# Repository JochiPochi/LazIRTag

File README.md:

# LaZIR Tag
Arduino based LaserTag System

BOM: https://docs.google.com/a/cyphyworks.com/spreadsheets/d/1MXdYDq4qyfqy3L1gnKtGEeZ4zqiRnnMYT2sN9ClZJ-U/edit?usp=sharing

REFERENCE:

IR Receiver Info - http://uk.farnell.com/vishay/tsop4838/ir-receiver-38khz/dp/4913190

IR Receiver Datasheet - http://www.farnell.com/datasheets/1693301.pdf

IR Reference - https://learn.adafruit.com/downloads/pdf/ir-sensor.pdf

Wifi Reference - https://espressif.com/en/products/esp8266/

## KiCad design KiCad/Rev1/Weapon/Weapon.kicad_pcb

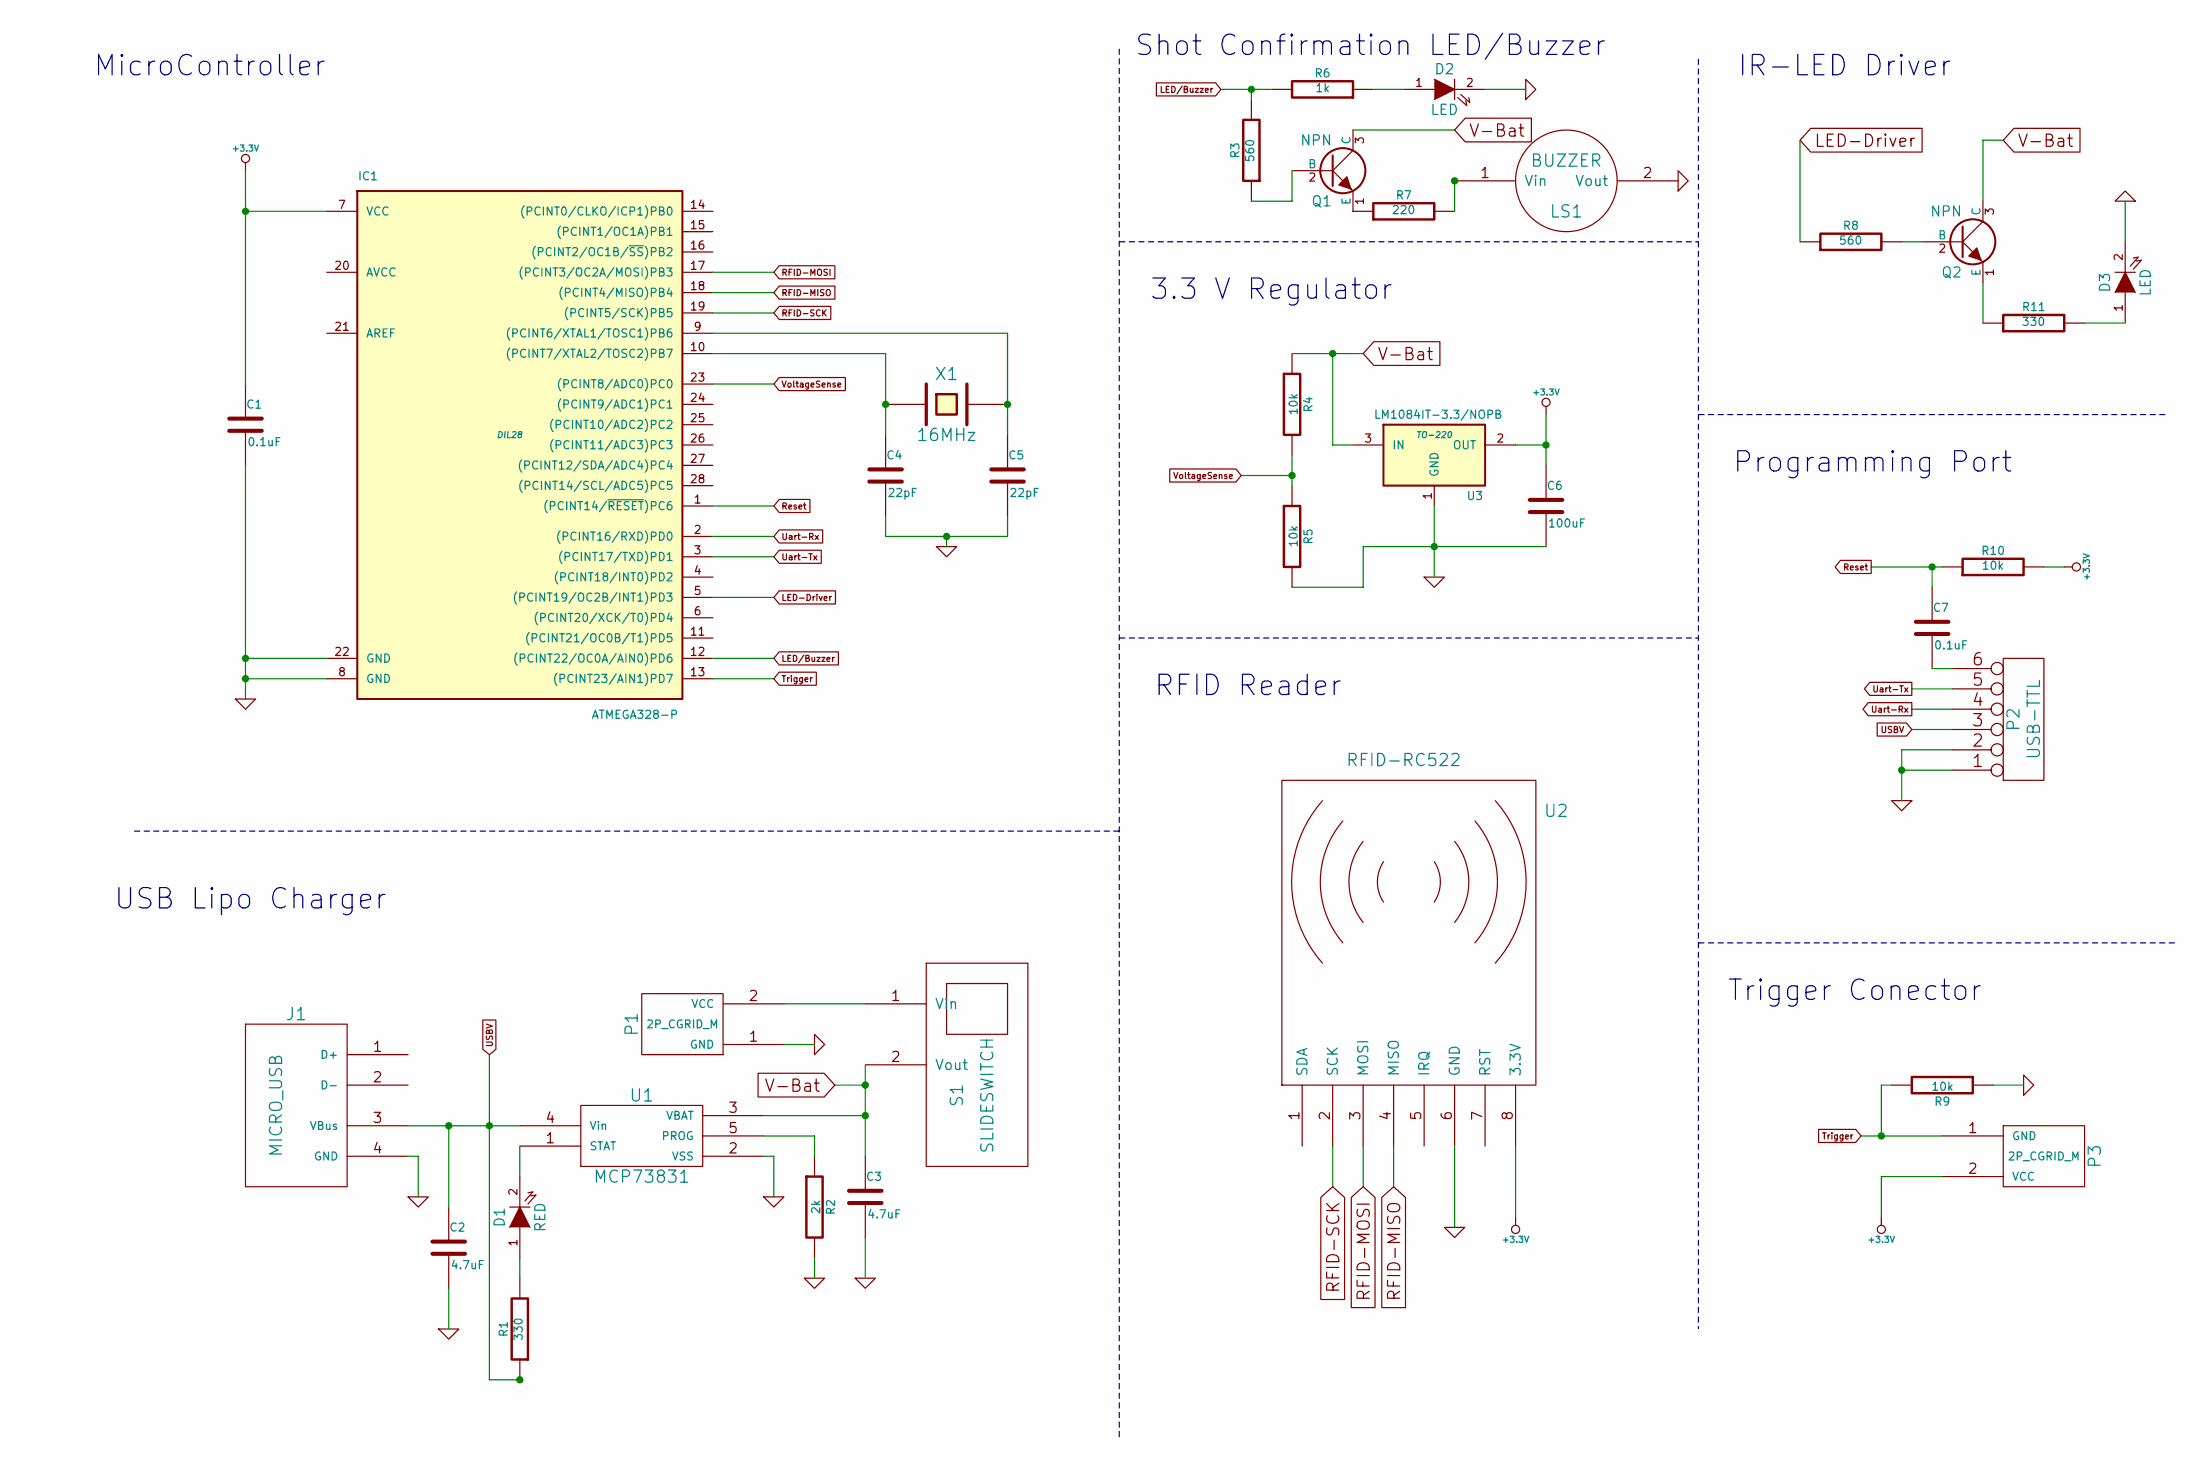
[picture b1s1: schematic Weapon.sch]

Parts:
C1, C7: 0.1uF
C2, C3: 4.7uF
C4, C5: 22pF
C6: 100uF
D1: RED
D2, D3: LED
IC1: ATMEGA328-P; DIL28
J1: MICRO_USB
LS1: BUZZER
P1: 2P_CGRID_M
P2: USB-TTL
P3: 2P_CGRID_M
Q1, Q2: NPN
R1, R11: 330
R2: 2k
R3, R8: 560
R4, R5, R9, R10: 10k
R6: 1k
R7: 220
S1: SLIDESWITCH
U1: MCP73831
U2: RFID-RC522
U3: LM1084IT-3.3/NOPB; TO-220
X1: 16MHz

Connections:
+3.3V: C1.1, C6.1, IC1.7 (VCC), P3.2 (VCC), R10.2, U2.8 (3.3V), U3.2 (OUT)
GND: C1.2, C2.2, C3.2, C4.2, C5.2, C6.2, D2.2 (K), D3.2 (K), IC1.8 (GND), IC1.22 (GND), J1.4 (GND), LS1.2 (Vout), P1.1 (GND), P2.1, P2.2, R2.2, R5.2, R9.1, U1.2 (VSS), U2.6 (GND), U3.1 (GND)
LED-Driver: IC1.5 ((PCINT19/OC2B/INT1)PD3), R8.1
LED/Buzzer: IC1.12 ((PCINT22/OC0A/AIN0)PD6), R3.2, R6.2
unnamed: P1.2 (VCC), S1.1 (Vin)
unnamed: D1.2 (K), U1.1 (STAT)
unnamed: D1.1 (A), R1.2
unnamed: R2.1, U1.5 (PROG)
unnamed: Q1.2 (B), R3.1
unnamed: Q1.1 (E), R7.1
unnamed: LS1.1 (Vin), R7.2
unnamed: D2.1 (A), R6.1
unnamed: C5.1, IC1.9 ((PCINT6/XTAL1/TOSC1)PB6), X1.2
unnamed: C4.1, IC1.10 ((PCINT7/XTAL2/TOSC2)PB7), X1.1
unnamed: C7.2, P2.6
unnamed: Q2.2 (B), R8.2
unnamed: D3.1 (A), R11.2
unnamed: Q2.1 (E), R11.1
RFID-MISO: IC1.18 ((PCINT4/MISO)PB4), U2.4 (MISO)
RFID-MOSI: IC1.17 ((PCINT3/OC2A/MOSI)PB3), U2.3 (MOSI)
RFID-SCK: IC1.19 ((PCINT5/SCK)PB5), U2.2 (SCK)
Reset: C7.1, IC1.1 ((PCINT14/~RESET~)PC6), R10.1
Trigger: IC1.13 ((PCINT23/AIN1)PD7), P3.1 (GND), R9.2
USBV: C2.1, J1.3 (VBus), P2.3, R1.1, U1.4 (Vin)
Uart-Rx: IC1.2 ((PCINT16/RXD)PD0), P2.4
Uart-Tx: IC1.3 ((PCINT17/TXD)PD1), P2.5
V-Bat: C3.1, Q1.3 (C), Q2.3 (C), R4.1, S1.2 (Vout), U1.3 (VBAT), U3.3 (IN)
VoltageSense: IC1.23 ((PCINT8/ADC0)PC0), R4.2, R5.1

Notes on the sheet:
MicroController
Shot Confirmation LED/Buzzer
3.3 V Regulator
RFID Reader
USB Lipo Charger
IR-LED Driver
Programming Port
Trigger Conector

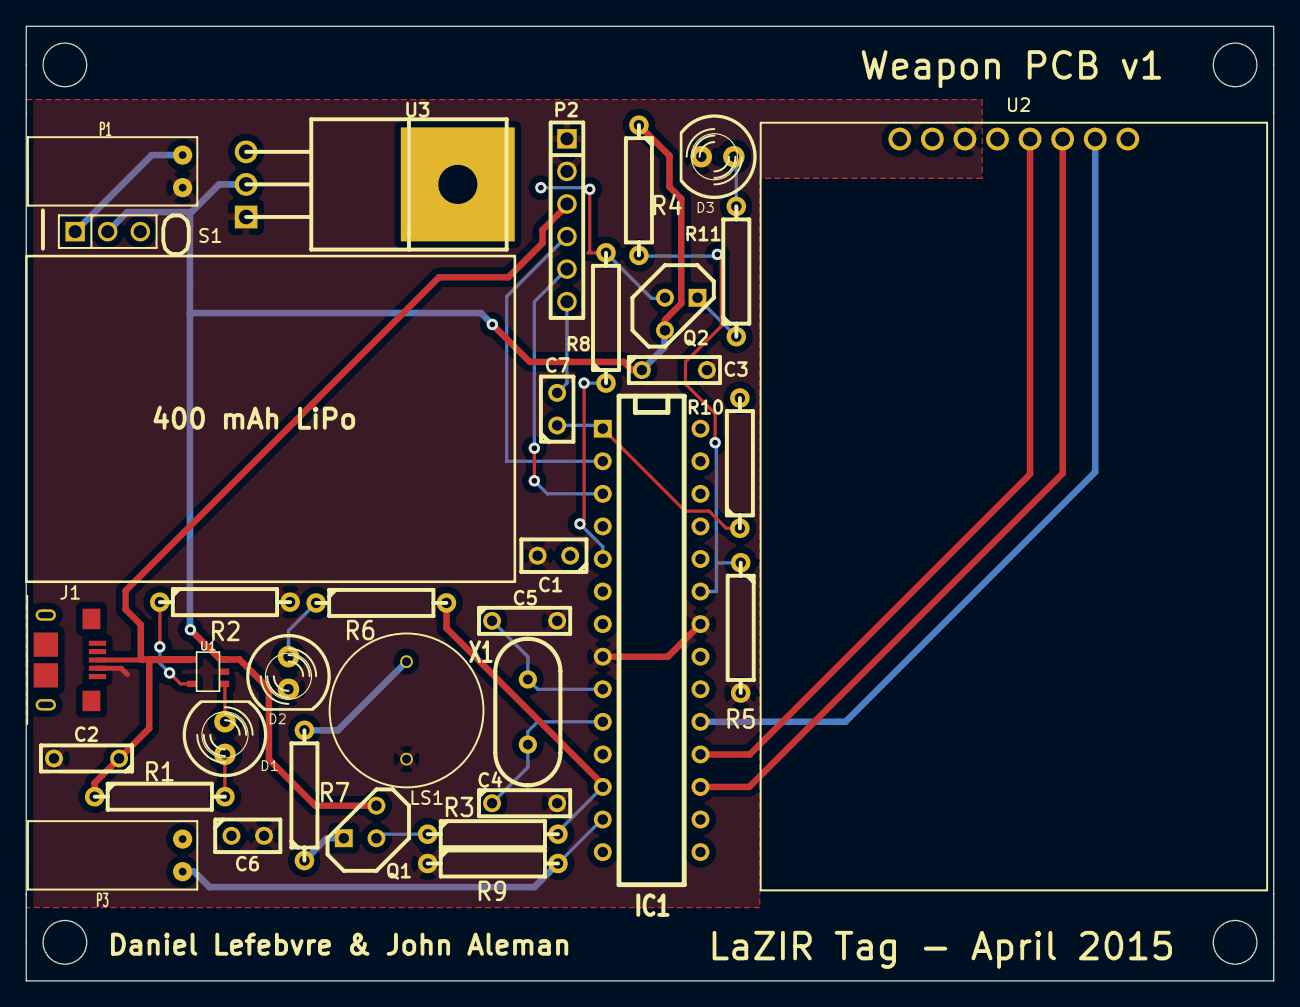
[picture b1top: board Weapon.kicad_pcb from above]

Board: 2 copper layers, 97.3 x 74.4 mm, 34 parts (0 on the bottom side), 28 nets.

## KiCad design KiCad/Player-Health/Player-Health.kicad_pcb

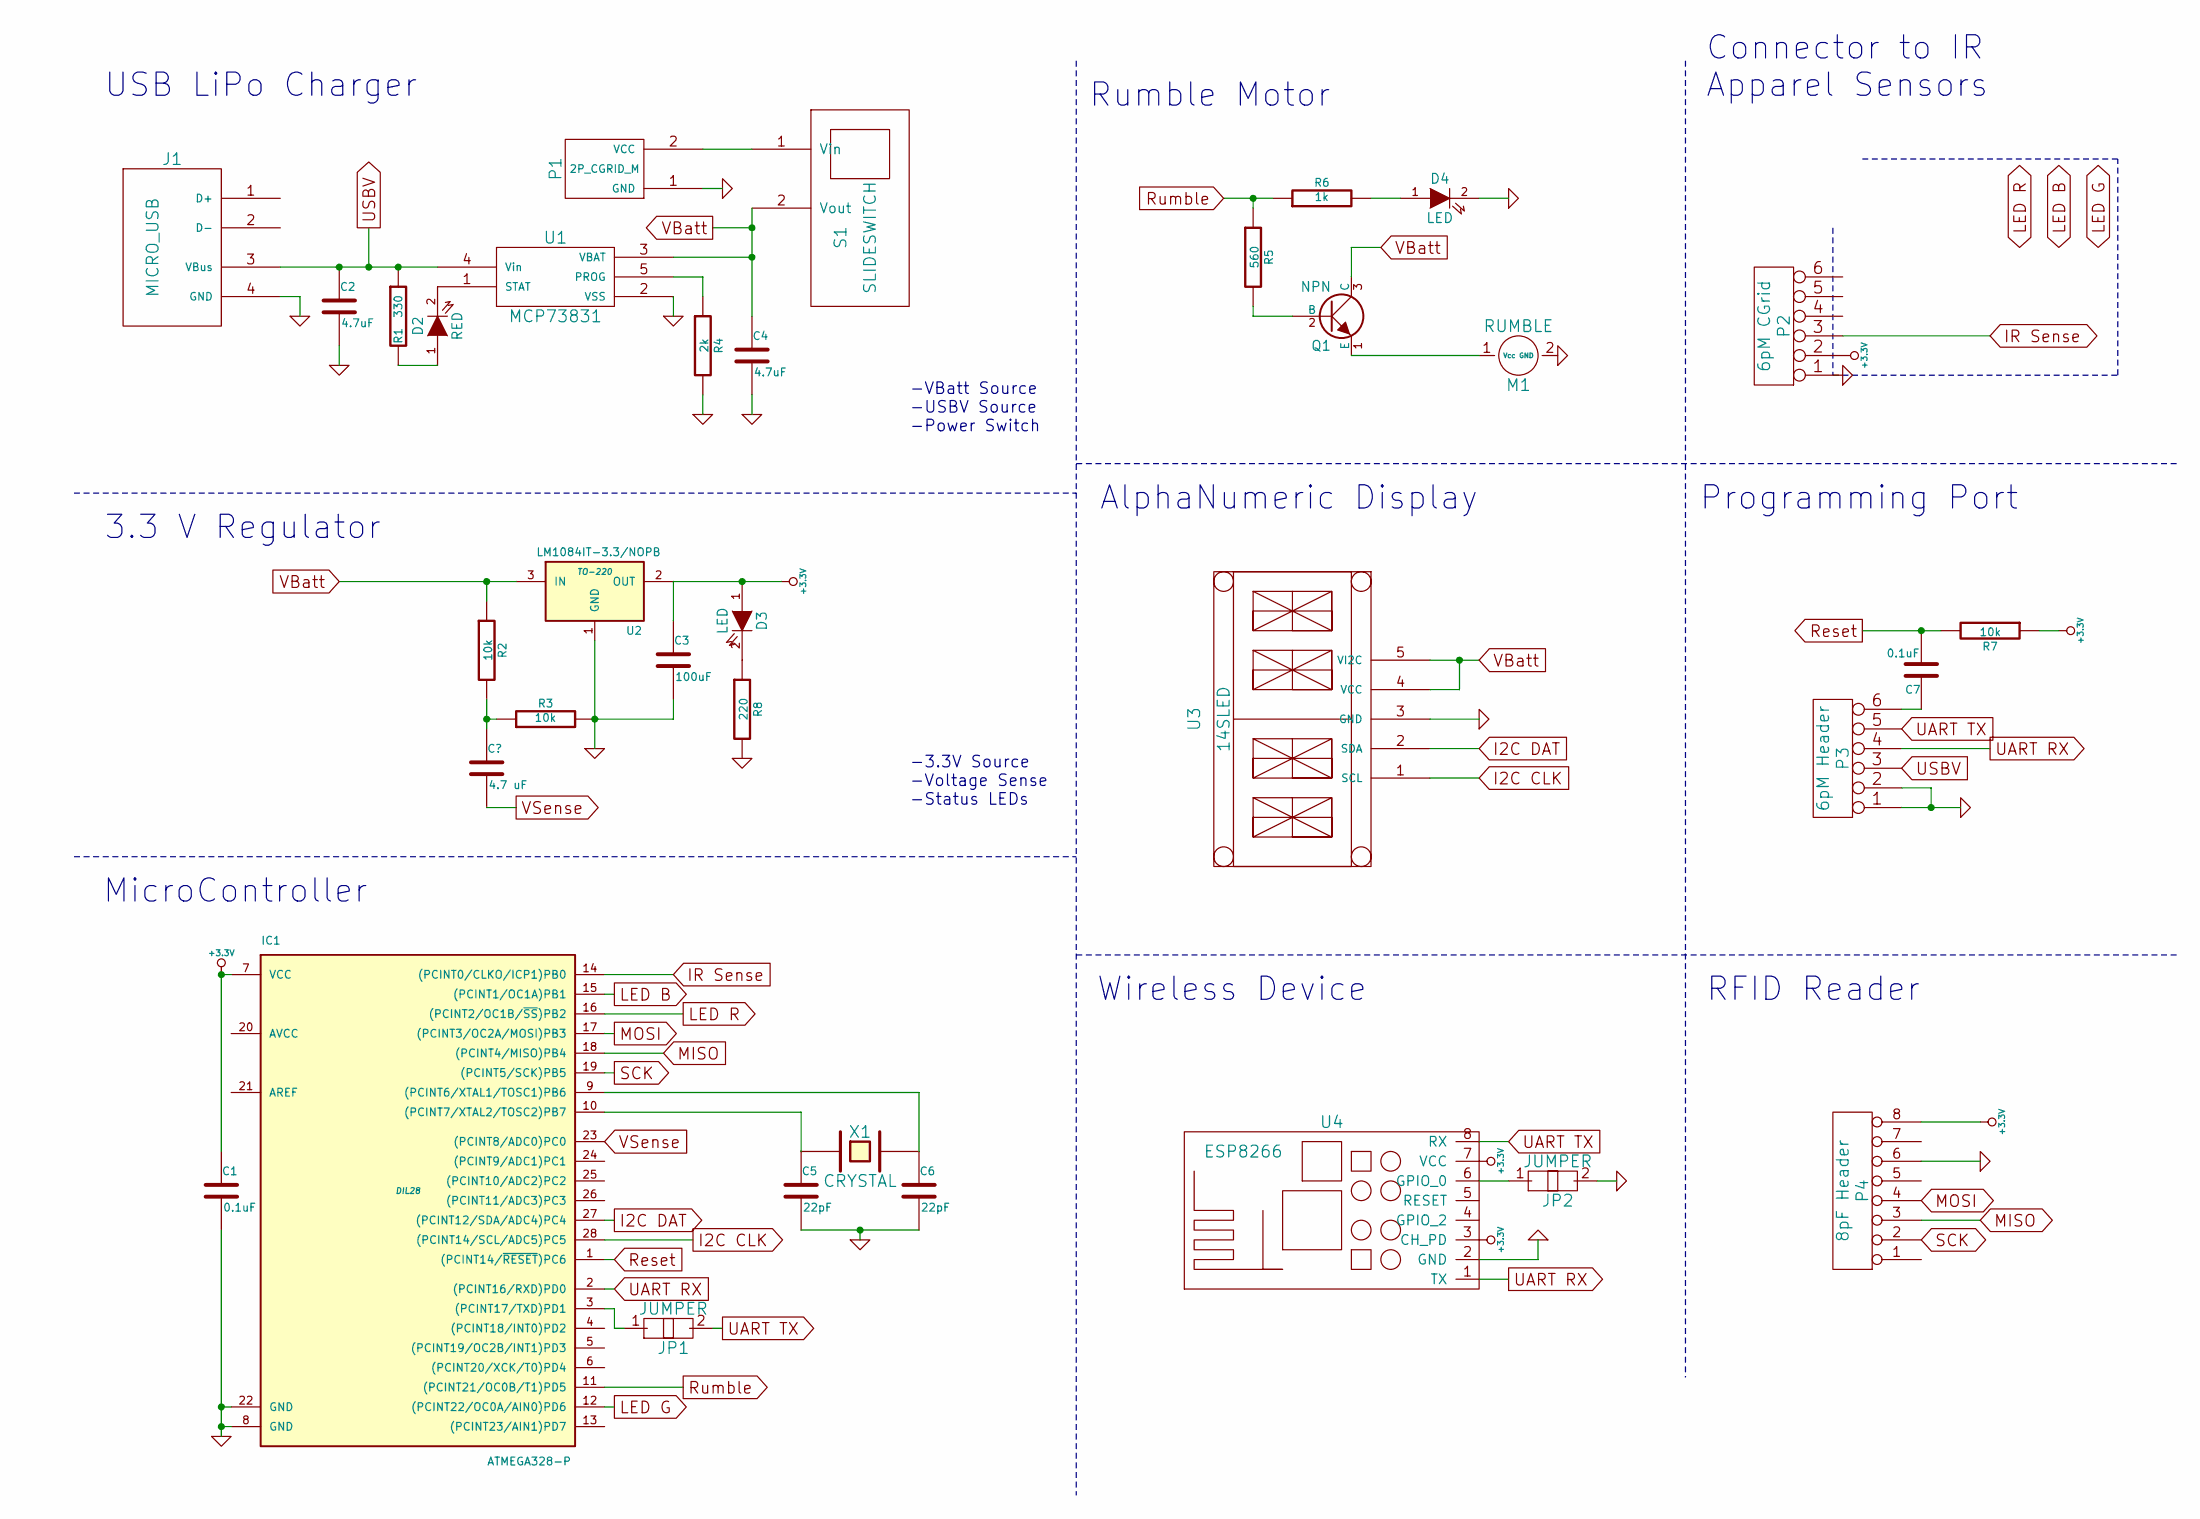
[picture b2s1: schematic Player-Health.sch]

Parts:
C1, C7: 0.1uF
C2, C4: 4.7uF
C3: 100uF
C5, C6: 22pF
D2: RED
D3, D4: LED
IC1: ATMEGA328-P; DIL28
J1: MICRO_USB
JP1: JUMPER
JP2: JUMPER
M1: RUMBLE
P1: 2P_CGRID_M
P2: 6pM CGrid
P3: 6pM Header
P4: 8pF Header
Q1: NPN
R1: 330
R2, R3, R7: 10k
R4: 2k
R5: 560
R6: 1k
R8: 220
S1: SLIDESWITCH
U1: MCP73831
U2: LM1084IT-3.3/NOPB; TO-220
U3: 14SLED
U4: ESP8266
X1: CRYSTAL

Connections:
+3.3V: C1.1, C3.1, D3.1 (A), IC1.7 (VCC), P2.2, P4.8, R7.1, U2.2 (OUT), U4.3 (CH_PD), U4.7 (VCC)
GND: C1.2, C2.2, C3.2, C4.2, C5.2, C6.2, D4.2 (K), IC1.8 (GND), IC1.22 (GND), J1.4 (GND), JP2.2, M1.2 (GND), P1.1 (GND), P2.1, P3.1, P3.2, P4.6, R3.2, R4.2, R8.2, U1.2 (VSS), U2.1 (GND), U3.3 (GND), U4.2 (GND)
I2C CLK: IC1.28 ((PCINT14/SCL/ADC5)PC5), U3.1 (SCL)
I2C DAT: IC1.27 ((PCINT12/SDA/ADC4)PC4), U3.2 (SDA)
IR Sense: IC1.14 ((PCINT0/CLKO/ICP1)PB0), P2.3
LED B: IC1.15 ((PCINT1/OC1A)PB1), P2.5
LED G: IC1.12 ((PCINT22/OC0A/AIN0)PD6), P2.4
LED R: IC1.16 ((PCINT2/OC1B/~SS~)PB2), P2.6
MISO: IC1.18 ((PCINT4/MISO)PB4), P4.3
MOSI: IC1.17 ((PCINT3/OC2A/MOSI)PB3), P4.4
unnamed: D2.1 (A), R1.2
unnamed: R4.1, U1.5 (PROG)
unnamed: JP2.1, U4.6 (GPIO_0)
unnamed: P1.2 (VCC), S1.1 (Vin)
unnamed: D4.1 (A), R6.2
unnamed: Q1.2 (B), R5.2
unnamed: M1.1 (Vcc), Q1.1 (E)
unnamed: C7.1, P3.6
unnamed: D3.2 (K), R8.1
unnamed: IC1.3 ((PCINT17/TXD)PD1), JP1.1
unnamed: C6.1, IC1.9 ((PCINT6/XTAL1/TOSC1)PB6), X1.2
unnamed: C5.1, IC1.10 ((PCINT7/XTAL2/TOSC2)PB7), X1.1
unnamed: D2.2 (K), U1.1 (STAT)
Reset: C7.2, IC1.1 ((PCINT14/~RESET~)PC6), R7.2
Rumble: IC1.11 ((PCINT21/OC0B/T1)PD5), R5.1, R6.1
SCK: IC1.19 ((PCINT5/SCK)PB5), P4.2
UART RX: IC1.2 ((PCINT16/RXD)PD0), P3.4, U4.1 (TX)
UART TX: JP1.2, P3.5, U4.8 (RX)
USBV: C2.1, J1.3 (VBus), P3.3, R1.1, U1.4 (Vin)
VBatt: C4.1, Q1.3 (C), R2.1, S1.2 (Vout), U1.3 (VBAT), U2.3 (IN), U3.4 (VCC), U3.5 (VI2C)

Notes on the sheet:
USB LiPo Charger
-VBatt Source -USBV Source -Power Switch
3.3 V Regulator
-3.3V Source -Voltage Sense -Status LEDs
AlphaNumeric Display
MicroController
Wireless Device
Connector to IR Apparel Sensors
Programming Port
RFID Reader
Rumble Motor

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
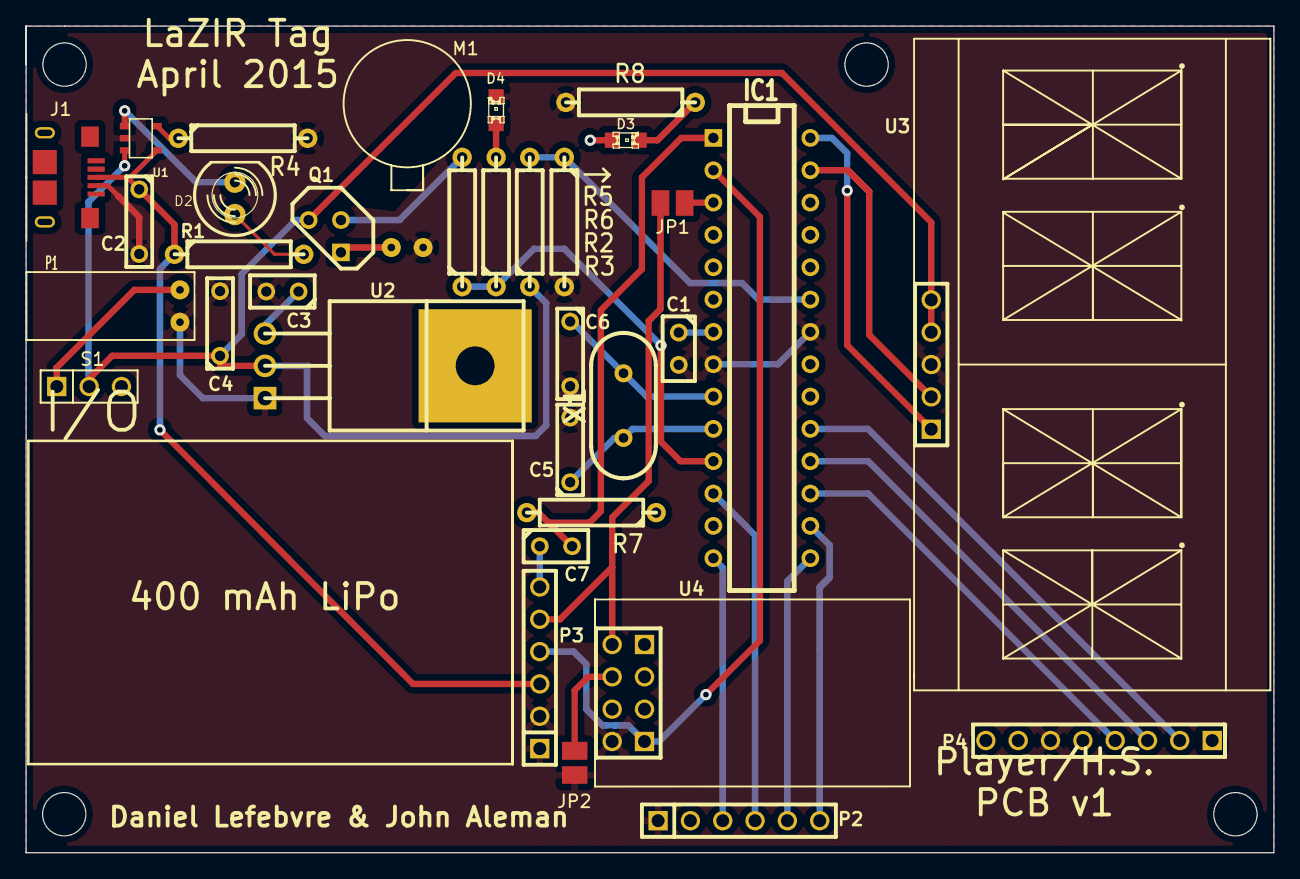
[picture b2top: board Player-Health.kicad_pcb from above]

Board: 2 copper layers, 98.0 x 64.9 mm, 34 parts (0 on the bottom side), 31 nets.

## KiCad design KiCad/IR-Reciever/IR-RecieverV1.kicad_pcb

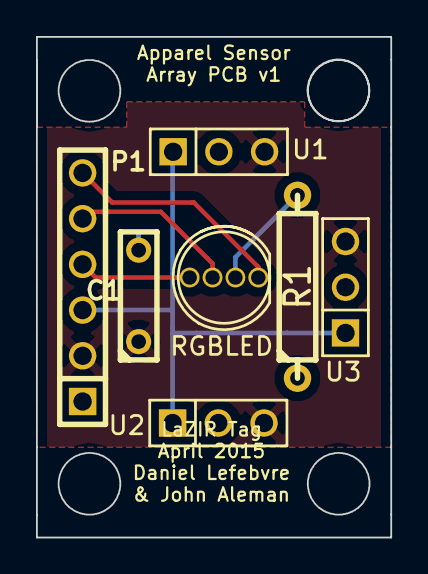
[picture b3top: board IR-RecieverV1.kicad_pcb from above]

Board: 2 copper layers, 19.7 x 27.8 mm, 7 parts (0 on the bottom side), 7 nets.

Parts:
C1: 100 uF; C2
P1: CONN_6; PIN_ARRAY-6X1
R1: 220; R4
U1, U2, U3: TSOP38238; PIN_ARRAY_3X1
U4: RGBLED; RGB-Led

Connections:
GND: C1.2, P1.1, R1.1, U1.2, U2.2, U3.2
unnamed: P1.3, U1.1, U2.1, U3.1
unnamed: P1.4, U4.4
unnamed: P1.5, U4.3
unnamed: R1.2, U4.2
unnamed: P1.6, U4.1
VCC: C1.1, P1.2, U1.3, U2.3, U3.3

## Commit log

2015-02-05 AdaFruit base code
2015-02-07 Create AppleTVPlayPause.ino
    This program is supposed to send the play/pause packet from the Apple remote. Sorry it isn't commented well yet.
2015-02-07 Rename AppleTVPlayPause.ino to Apple-TV/AppleTVPlayPause.ino
2015-02-07 Rename AppleTV-PlayPause Sequence.txt to Apple-TV/AppleTV-PlayPause Sequence.txt
2015-02-10 Rename UART.txt to UART/Packets.txt
2015-02-11 Create MsgType 0B Test
    Configuring how to send customized packets.
2015-02-12 Firmware folders for the different components added
2015-02-12 Started adding common libraries
2015-02-13 A bit more progress on the IR library, it can now send just fine, working on the reading
2015-02-13 More progress on IR Library
2015-02-14 This is very broken code for the Gun FW I'll branch, fix and merge
2015-02-14 Woot Interrupt working but I still need to make it save to the circular buffer
2015-02-16 Create Rx_Structs.ino
    This iteration of the test .ino allows for received packets to be read and all of the bytes to be saved into the proper data type. There is no checking of the checksum yet, but all of the packets tra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
2015-02-16 Yo I have added wifi references to the read me
2015-02-16 Added temp Player_FW
    A bit about system capability requirements
2015-02-16 Adding most recent Serial test codes
    Combination of RX_structs and TX_6Buttons currently does not work.
    Debugging as you read
2015-02-16 Cleaning up a bit, still buggy
2015-02-16 1 byte tansmission works but for some reason it break down with more. So close for it to work!
2015-02-19 Last known state of IR byte transmission by packet lenght, all forward will be on byte lenght. New branch until that works
2015-02-19 IR library works! now I'm just cleaning up code and commenting
2015-02-19 Works pin to pin, currently editting for 38khz
2015-02-19 WOOOOOOOT IR library working with 38khz signal. More testing is necessary but bytes come without corruption now. a bit slower than I would have wanted but oh well
2015-02-26 Catching up
    Going to submit the changes then take a fresh approach
2015-02-26 Catching up
2015-03-07 Kicad Init
2015-03-12 Adding more KiCad material
    Second revision of apparel sensors and start of wrist display project
2015-03-12 Moved component library
2015-03-12 Started on the PCB design for the Weapon
2015-03-12 Started Schematic for Wrist Display
    Includes MicroUSB charging shematic
2015-03-12 Library Updates
2015-03-12 Added Wireless Device
    Component in Library
2015-03-12 Weapon Schematic Ready
2015-03-12 Updated Components - 2:45 AM
    Nearly all of the weapon components delegated
2015-03-20 3/19 Progress
    KiCad - weapon component to module selection and pcb file created.
    All schematic components on net and allocated
2015-03-29 3/29 KiCad Updates
    Revised Weapon PCB, renamed wrist display unit and more
2015-03-29 Revert "3/29 KiCad Updates"
    This reverts commit a2529da1b40b1f6e0e832ed1976ed3be41434859.
2015-03-29 Revert "Revert "3/29 KiCad Updates""
    This reverts commit 46467126b97e8d3ee2ff82587e11af580e6d6854.
2015-04-10 Through Holes & Player/Health Schematic
    I'm re-uploading the Apparel Sensor and Weapon PCBs with extended edges
    and through holes on the corners for mounting. This also includes the
    first draft of the Player/Health Schematic. Please critique
2015-04-17 Quick Update #1 4/16
2015-04-17 Quick Update #2 4/16
2015-04-17 Quick Update #3 4/16
2015-04-17 Quick Update #4 4/16
2015-04-17 Quick Update #5 4/16
2015-04-17 Quick Update #6 4/16
    Hopefully the last changes to the ir receiver pcb and weapon pcb
2015-04-17 Quick Update #1 4/17
    Finished PCBs for Apparel Sensor and Weapon, ready for review
    Finished Schematic, Netlist, and Component Assignment for Player/Health
    Started PCB with components and text for Player/Health
    New Component footprints for 8x1 pin array, wifi module, and
    alphanumeric
2015-04-17 Quick Update #2 4/17
    Added Jumpers to Schematic, Net List and PCB, but failing connectivity
2015-04-17 Quick Update #3 4/17
2015-04-17 Last Update for the Night 4/17(4/16)
    General PCB layout, fix to jumper pads
2015-04-17 Update #1 4/17
    First Draft of Player/Health PCB for review.
    Added on/off indicators to weapon pcb for slideswitch
2015-04-17 Update #2 4/17
    Shrunk board to be >10cm
2015-04-24 Quick Update #1 4/24
2015-04-24 Quick Update #2 4/24
2015-04-24 Quick Update #3 4/24
    Adjusted keepout areas
2015-04-24 Quick Update #4 4/24
2015-04-24 Quick Update #5 4/24
2015-04-24 Quick Update #6 4/24
2015-04-29 Quick Update #1 4/28
    Added resistor (220) to buzzer in weapon sch,net,pcb
2015-04-29 Quick Update #2 4/28
    Changes to Weapon PCB
2015-04-29 Quick Update #3 4/28
    Refinement of text placement
2015-04-29 Ordered Weapon Proto
    Tada... Holy Crap
2015-04-29 Final Push 4/28ish
    Updated Formatting of Player/Health PCB
2015-05-01 Quick Update 5/1
2015-05-01 Quick Update #2 5/1
    Night night
2015-05-01 Quick Update #3 5/1
    Potential last changes before ordering ir receiver and player boards
2015-05-01 Quick Update #4 5/1
    Added gerber files to order boards
2015-05-01 Quick Update #5 5/1
    Added .zip folders and .png images from processed orders.
2015-05-22 Started the Code for the Central System. This is the first shot at it and is still incomplete.
2015-09-11 First pass at the Database Class
2015-09-11 Central System code builds. Implementation is still a bit flimsy though and CentralSystem.cpp should only be used as reference
2015-09-12 CentralSystem: Major refactoring of central system
    Refactored from Eclipse project structure to straight
    GNU Make.
    Refactored organization and catagorization of devices
    by implementing a class for each device type.
    Removed irrelevant files.
2015-09-12 CentralSystem: Removed Eclipse project files
    Removed Eclipse project files from the central system
    project.
2015-09-12 CentralSystem: Fixed typo which resulted build failure
2015-09-13 CentralSystem: WIP: Continuing major refactoring.
    General refactoring.
    wrote methods for Players class.
2015-09-16 CentralSystem: Added more player methods
2015-09-30 CentralSystem: WIP: continued development on player methods
2015-11-03 Gerber Files
    Weird git stash business saved gerber files, I guess
2016-04-13 Update Packets.txt
    A lot of structure here was made before we selected WiFi as the wireless interface. Simplified the protocol to reflect that.
2016-04-13 Update README.md
    Include a short decription of the system and links for more information
2016-04-13 Management: Create Ideas&Requirements.txt
2016-04-13 Management: Add serial and IR protocol description document
